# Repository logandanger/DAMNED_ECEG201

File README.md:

# DAMNED_ECEG201

Interactive OS and desktop simulator for DANGER, prototype #1: a generative beat maker built on preloaded samples. The hardware is the Bucknell ECEG 201 DAMNED board (ESP32-S3) plus Adafruit I2C breakouts.

This README is the single reference for the circuit. Everything below was extracted from the KiCad files in `hardware/kicad/` (the netlist is generated from the `.kicad_pcb`, so it reflects the routed board). Items marked **[verify]** were not provable from the files and need a check on the physical board or datasheet.

## Contents

1. [Repo layout](#1-repo-layout)
2. [Prototype #1 concept](#2-prototype-1-concept), [behavior](#beat-maker-behavior), [control map](#control-map)
3. [System block diagram](#3-system-block-diagram)
4. [Power](#4-power)
5. [ESP32-S3 module and pin map](#5-esp32-s3-module-and-pin-map)
6. [Display](#6-display)
7. [Buttons, slide switch, debounce](#7-buttons-slide-switch-and-debounce)
8. [I2C bus and add-on devices](#8-i2c-bus-and-add-on-devices)
9. [Audio path](#9-audio-path)
10. [LEDs](#10-leds)
11. [USB-C](#11-usb-c)
12. [CAN bus](#12-can-bus)
13. [Connectors, headers, jumpers, test points](#13-connectors-headers-jumpers-and-test-points)
14. [Free resources](#14-free-resources)
15. [Risks and open issues](#15-risks-and-open-issues)
16. [Planned software architecture](#16-planned-software-architecture)
17. [Bill of materials](#17-bill-of-materials)
18. [Course context](#18-course-context)

---

## 1. Repo layout

| Path | Contents |
|---|---|
| `hardware/kicad/` | KiCad 10 project: `NewBoard PCB v1.10 - DA2 no LDO` (`.kicad_pro/.kicad_sch/.kicad_pcb/.kicad_prl`) and the `LEDs` sub-sheet `sheet1.kicad_sch`. File names keep their spaces because the `.kicad_pro` references them by name. |
| `hardware/netlist/netlist.json` | Every net with its pins `[ref, pad, pin function]`, extracted from the PCB. Machine-readable. |
| `hardware/netlist/esp32_pinmap.csv` | ESP32-S3 module pin, pin function, net. |
| `docs/prototype1-sketch.jpg` | Hand sketch of the prototype #1 layout and parts list. |
| `docs/DA2-PCB-Layout-in-KiCad.pdf` | Course assignment 2 (KiCad layout). |
| `docs/DA8-DAMNED-Assembly.pdf` | Course assignment 8 (assembly and CircuitPython test). |
| `docs/DAMNED-sensors-2026-11.pdf` | Course-approved Adafruit parts list. |
| `docs/controls.md` | Control mapping, A/B chord logic, conflicts. |
| `docs/architecture.md` | Software structure, real-time rules, CPU and RAM budgets. |
| `docs/mirror-protocol.md` | Framebuffer protocol for `--mirror`. |
| `core/` | Beat engine, sampler, reverb, UI, app logic, mirror protocol. No hardware access. |
| `core/config/beat_config.hpp` | Every tunable: commit time, fades, loop, grid, layers, mutation, drums, hold times. |
| `core/samples/sample_data.cpp` | Generated sample data (flash). Do not edit; run `tools/pack_samples.py`. |
| `samples/` | Source WAVs and `manifest.csv`. |
| `tools/` | `build_sim.py`, `make_samples.py` (placeholder set), `pack_samples.py` (WAV to C++). |
| `core/config/control_map.hpp` | Every control-to-function mapping. |
| `hal/` | `hal.hpp` interface; `esp32/` and `sim/` implementations. |
| `firmware/` | ESP-IDF entry point, tasks, mirror sender, PlatformIO project. |
| `sim/` | SDL2 simulator. |
| `tests/` | Unit tests, whole-app tests, benchmark. |

Assembly guide (not mirrored): <https://bucknellmakers.dozuki.com/Guide/DAMNED+Project+Assembly/144?lang=en>

## 2. Prototype #1 concept

Source: `docs/prototype1-sketch.jpg`.

- **Base:** DAMNED PCB (6 tactile buttons, 320x240 display, ESP32-S3).
- **Keys:** Adafruit AW9523 GPIO expander (16 pins) for a 12-key chromatic octave, plain on/off (no velocity in prototype #1; deferred).
- **Encoders:** two Adafruit I2C STEMMA QT rotary encoders (bottom right, position may change).
- **Audio:** Adafruit TLV320DAC3100 I2S DAC with headphone and speaker output, driving a mono enclosed 3 W 4 ohm speaker. The separate PAM8302 amp was dropped (the DAC3100 has its own class-D speaker driver).
- **Light strip:** 2x16 DotStar LEDs behind a foggy acrylic panel, under the screen.
- **Power:** USB-C only for prototype #1.
- **Sketch layout:** screen center; d-pad left; A/B right of screen; speaker grille top right; encoders bottom right; 12 keys across the bottom (7 white, 5 black).
- **Sound engine:** generative beat maker on preloaded samples. No synthesis on the device.

### Beat maker behavior

You play; the box turns what you played into a loop, adds drums, and keeps it slowly changing.

- **Loop:** 4 bars of 4/4 on a 16th grid, 64 steps. At tempo $B$ in BPM one step lasts $t_\text{step} = \frac{60}{4B}\ \text{s}$, e.g. 125 ms at 120 BPM. The transport always runs; the screen shows its position.
- **Melodic keys** (the 8 non-pad keys) play the current instrument at once, pitched from its sample: $f = f_\text{root} \cdot 2^{(n - n_\text{root})/12}$. Each instrument plays in its sample's register.
- **Seeding:** everything played on the melodic keys is captured. The seed commits after **5 s** with no key held (`kSeedIdleCommit`). Holding a key postpones the commit.
- **Quantize:** on commit each note moves to the nearest 16th and its length to whole steps (1 to 16). Timing never has to be right. If nothing is playing, the loop restarts so the first note played lands on bar 1, beat 1.
- **Accumulate:** playing again on the same instrument adds to the same layer (same pitch on the same step merges). Selecting another instrument commits a pending seed at once and starts a new layer on the next seed.
- **Fade-in:** new or added notes ramp both the chance of playing and their velocity from 12 % to 100 % over **8 bars** (`kFadeInBars`).
- **Generative loop:** the first full pass is your exact quantized seed. After that, at each loop start, a layer mutates with an intensity that ramps over 6 loops to about 1.5 changes per loop: drop a note, add a note, octave shift, rhythm nudge of $\pm 1$ step, passing tone, or restore a changed note to the seed. Added and passing notes use only pitches and pitch classes you played; octave shifts stay within one octave of your range. The more a layer drifts, the more likely it moves back toward the seed.
- **Drums** (generated, on the 4 pad samples): silent until the first seed commits, then fade in over 8 bars. Kick on beat 1 and 3, snare on 2 and 4, hats on quarters, 8ths or 16ths, crash at each 4-bar phrase start, occasional open cymbal, ghost snares when busy, a snare fill in the last beat of some phrases. Density follows how many distinct steps your seeds use, plus a slow random walk. Extra kicks land on your strongest notes (velocity and length). Drums fade out when every layer is cleared.
- **Layers:** up to **4** (`kMaxLayers`), each with its own seed, mutation state and fade. A 5th fades the oldest out over 8 bars. Switching instrument never cuts anything: held notes ring until released, old loops keep playing.
- **Audio:** 32-voice sampler, 44.1 kHz stereo out, 22.05 kHz mono samples in flash. Every start ramps in over 2 ms; stolen or choked voices fade over 6 ms. Layer fades and clears are gain ramps, so nothing clicks. A cheap stereo reverb (4 combs, 4 allpasses) runs on both targets.
- **Samples:** placeholders rendered offline by `tools/make_samples.py`: drums `kick`, `snare`, `hat`, `crash`; instruments `keys`, `pluck`, `bass`, `bell`, `marimba`, `pad` (looped). To use real samples, replace WAVs in `samples/`, edit `samples/manifest.csv` (root note, loop points, release), run `python tools/pack_samples.py`, rebuild. Total budget 1.5 MB of flash; the placeholders use 515 kB.

### Control map

| Control | Function |
|---|---|
| Keys C# D# F# G# (top-left 4) | Drum pads: kick, snare, hat, crash. Play live over the loop; never captured. |
| Keys C D E F G A A# B | Current instrument, live; captured as the seed |
| A tap | Next instrument (cursor; the name turns red) |
| A hold 0.6 s | Select the instrument under the cursor |
| B tap | Previous instrument |
| A + B, release after 1 s | Clear current layer (fade 1.5 s). With only a pending seed on a new instrument, it drops that seed instead. |
| A + B, hold 3 s | Clear everything (fade 2.5 s), drums stop |
| Left encoder | Reverb, 2 % per detent |
| Right encoder | BPM, 60 to 180, 1 per detent; glides, loop stays in sync |
| D-pad, encoder pushes | Unassigned |

Taps fire on release, so pressing A and B together never steps or selects; see `docs/controls.md` for the full chord logic. The screen shows instrument, BPM, reverb, the loop position across 4 bars, each layer with its fade state (red mark = the layer A+B clears), the seed countdown, and A/B hold progress with a mark at 1 s.

## 3. System block diagram

```mermaid
flowchart LR
  USB[USB-C J4] -->|+5V| ESD[USBLC6 U1]
  USB -->|VBUS| D4[B540C D4] --> VCC[VCC rail]
  BAT[Battery J1] --> Q1[PMOS Q1] --> VCC
  VCC --> LDO[TLV75733 U3] -->|JP2| V33[+3V3]
  V33 --> ESP[ESP32-S3-WROOM-1 U2]
  ESD -->|D+/D-| ESP
  ESP -- SPI + DC/RST/BL --> LCD[ST7789 320x240 via FFC J6]
  ESP -- I2C GPIO3/4 --> I2C{{I2C bus}}
  I2C --> ADC[MCP3221A5 0x4D]
  I2C --> J2[J2/J5/J8 STEMMA QT]
  J2 -.-> AW[AW9523 keys]
  J2 -.-> ENC[2x rotary encoders]
  J2 -.-> DAC[TLV320DAC3100]
  ESP -- I2S GPIO5/6/7 --> J3[J3 I2S port] -.-> DAC
  ESP -- GPIO17/18 --> LED[20x SK9822 on board]
  BTN[6 buttons] --> DB[MC14490 debounce U4] --> ESP
  ESP -- TWAI GPIO15/16 --> CAN[TCAN3414 IC2] --> J15[J15 CAN]
```

Dotted lines are off-board Adafruit breakouts from the prototype #1 plan.

## 4. Power

### Topology

```mermaid
flowchart LR
  VBUS[+5V from USB-C] --> D4[D4 B540C-13-F Schottky] --> VCC
  VBUS --> Q1G[Q1 gate]
  BATT[+BATT J1 pin 2] --> Q1D[Q1 drain]
  Q1S[Q1 source] --> VCC
  VCC --> U3[U3 TLV75733PDBV 3.3 V LDO] --> JP2 --> V33[+3V3]
  V33 -->|JP1 solder jumper| VESP[V_ESP = ESP32 3V3 pin]
```

- **+5V** is raw USB VBUS. U1 (USBLC6-2SC6) clamps it, C3 (0.1 uF) decouples it, and R9 (100 k) pulls it to ground.
- **VCC** is the system rail, fed from either USB through D4 or the battery through Q1:
  - **USB present:** VCC is about VBUS minus the Schottky drop. Q1's gate sits at VBUS, so Q1 is off. Its body diode is reverse biased, so the battery is isolated.
  - **USB absent:** R9 pulls Q1's gate to ground. Q1 (DMP2045U, P-channel) turns on, and VCC equals the battery voltage minus a small $I R_{DS(on)}$ drop.
  - This is a standard P-MOSFET plus Schottky power-path OR.
- **No charger.** The board does not charge the battery. J1 is a JST-PH 2-pin (`S2B-PH-K-S`): pin 1 GND, pin 2 +BATT. There is no reverse-polarity protection.
- **+3V3** comes from U3 (TLV75733PDBV, 3.3 V LDO, SOT-23-5). IN and EN are both tied to VCC (always on), and C5 (10 uF) is the output cap. JP2 (2-pin header, shunt) sits between U3 OUT and the +3V3 net, so you can pull the shunt and insert a meter or an external supply.
- **V_ESP** is the ESP32 module's 3V3 pin. It reaches +3V3 only through JP1 (solder jumper, **default open**). JP1 must be bridged for the module to power up from this board. It also lets you measure ESP current.
- **VCC (5 V class) feeds:** U3 input, all 20 SK9822 LEDs, D3 power LED, header J7. **+3V3 feeds:** the ESP32 (via JP1), MCP3221, TCAN3414, MC14490, the display, pull-ups, I2C ports, J9.
- **Decoupling:** +3V3: C1 22 uF, C7/C9 10 uF, C2/C8/C10 0.1 uF. VCC: Cin1 10 uF, plus 0.1 uF at each LED (C13-C32).

### Power indicators

| LED | Fed from | Series R | Approx. current |
|---|---|---|---|
| D1 blue (`LTST-C250TBKT`) | V_ESP | R3 68 ohm | ~6 mA |
| D2 green (`LTST-C230GKT`) | +3V3 | R7 120 ohm | ~10 mA |
| D3 green | VCC | R8 300 ohm | ~10 mA |

$$I = \frac{V_s - V_f}{R}, \qquad \text{e.g. } \frac{3.3\ \text{V} - 2.9\ \text{V}}{68\ \Omega} \approx 6\ \text{mA}$$

(Forward voltages are typical for blue/green SMD LEDs; check the datasheets.)

### Budget (planning numbers)

- USB-C sink with 5.1 k pull-downs: the source offers at least 500 mA (USB 2.0), usually 1.5 A at 5 V. No USB-PD.
- 20 SK9822 LEDs at full white draw roughly 20 x 60 mA = 1.2 A worst case. Keep brightness low or the rail will sag. **[verify]** the datasheet current per LED.
- The DAC3100 speaker amp at 3 W into 4 ohm needs a sizeable 5 V current. Powering it from the 3V3 STEMMA port limits output power. **[verify]** against Adafruit's board docs before choosing the supply.

## 5. ESP32-S3 module and pin map

U2 is an **ESP32-S3-WROOM-1** (dual-core Xtensa LX7, 240 MHz, Wi-Fi + BLE, native USB). The flash/PSRAM variant is not specified in the files **[verify]**: see risk R1 in section 15.

Full table: `hardware/netlist/esp32_pinmap.csv`.

| GPIO | Module pin | Net | Function |
|---|---|---|---|
| EN | 3 | RESET | Reset button SW2; R6 5.1 k pull-up, C4 1 uF |
| 0 | 27 | BOOT | Boot-mode button SW1 |
| 1 | 39 | GPIO1 | Header J12 pin 5 |
| 2 | 38 | DISP_BL | Display backlight (J6 pin 8) |
| 3 | 15 | I2C_SDA | I2C data (strapping pin, see note) |
| 4 | 4 | I2C_SCL | I2C clock |
| 5 | 5 | I2S_LRCLK | I2S word select (J3 pin 4) |
| 6 | 6 | I2S_SDATA | I2S data out (J3 pin 3) |
| 7 | 7 | I2S_BLCK | I2S bit clock (J3 pin 2) |
| 8 | 12 | A5 | MCP3221 analog input net, TP18, header J12 pin 6 |
| 9 | 17 | D9 | Header J12 pin 2 |
| 10 | 18 | SW_Sli | Slide switch S1 |
| 11 | 19 | SW_Do | Debounced Down |
| 12 | 20 | SW_Uo | Debounced Up |
| 13 | 21 | SW_Ro | Debounced Right |
| 14 | 22 | SW_Lo | Debounced Left |
| 15 | 8 | TWAI_RX | CAN RXD (TCAN3414) |
| 16 | 9 | TWAI_TX | CAN TXD (TCAN3414) |
| 17 | 10 | DS_CLK | LED chain clock |
| 18 | 11 | DS_DATA | LED chain data |
| 19 | 13 | USB_D- | USB (through U1) |
| 20 | 14 | USB_D+ | USB (through U1) |
| 21 | 23 | SW_Ao | Debounced A |
| 35 | 28 | SPI_MOSI | Shared SPI bus |
| 36 | 29 | SPI_SCK | Shared SPI bus |
| 37 | 30 | SPI_MISO | Shared SPI bus |
| 38 | 31 | UART_RX | Header J10 pin 1 |
| 39 | 32 | UART_TX | Header J10 pin 2 |
| 40 | 33 | DISP_DC | Display data/command |
| 41 | 34 | DISP_RST | Display reset |
| 42 | 35 | SPI_CS1 | Display chip select |
| 43 (TXD0) | 37 | SPI_CS3 | SPI port J14 chip select |
| 44 (RXD0) | 36 | SPI_CS2 | SPI port J13 chip select |
| 45 | 26 | GPIO45 | Header J12 pin 4 (strapping pin) |
| 46 | 16 | GPIO46 | Header J12 pin 1 (strapping pin) |
| 47 | 24 | SW_Bo | Debounced B |
| 48 | 25 | GPIO48 | Header J12 pin 3 |

Notes:
- GPIO0, 3, 45, 46 are strapping pins. Keep their boot-time levels in mind when attaching peripherals (GPIO3 has the I2C pull-up, which is harmless at boot).
- GPIO43/44 are the default UART0 console pins, repurposed here as SPI chip selects. Console output over UART0 is not available; use USB CDC (native USB) for logs.
- GPIO39-42 are the JTAG pins; the board uses them as UART and display control. Debug through the USB-Serial-JTAG peripheral instead.

## 6. Display

- **Panel:** 320x240, ST7789 driver, SPI, colour, no touch (`320x240_SPI_ST7789_FFC`, reference DISP1).
- **Connector:** J6, `FFC3B07-08-T`, 8-pin FFC. FFC connectors wear out; open and close them sparingly (assembly guide).

| J6 pin | Signal | ESP32 |
|---|---|---|
| 1 | GND | |
| 2 | 3V3 | |
| 3 | SCK | GPIO36 |
| 4 | MOSI | GPIO35 |
| 5 | RST | GPIO41 |
| 6 | DC | GPIO40 |
| 7 | CS | GPIO42 (SPI_CS1) |
| 8 | Backlight | GPIO2 |

- The backlight is driven straight from a GPIO (no transistor on the schematic), so PWM dimming works through the LEDC peripheral but the display's backlight current must stay within the GPIO limit **[verify]**.
- Framebuffer size: $320 \times 240 \times 2\ \text{B} = 153{,}600\ \text{B}$ (RGB565). A full frame at SPI 40 MHz takes $153{,}600 \times 8 / 40\times10^{6} \approx 31\ \text{ms}$, so 30 fps needs partial updates or a faster clock (the ST7789 usually tolerates 40 to 80 MHz **[verify]**). LVGL partial buffers and dirty-rectangle updates handle this.

## 7. Buttons, slide switch and debounce

Six tactile inputs are hardware-debounced by **U4, MC14490** (hex contact-bounce eliminator, SOIC-16). The debounce time is set by **C12 (100 pF)** across OSCIN/OSCOUT **[verify]** the exact delay in the MC14490 datasheet for 3.3 V.

| Button | Switch | Raw net (to U4 input) | Debounced net (U4 output) | GPIO |
|---|---|---|---|---|
| Up | SW5 `TS02-66-50` | SW_U (AIN pin 1) | SW_Uo (pin 15) | 12 |
| Down | SW6 | SW_D (FIN pin 10) | SW_Do (pin 6) | 11 |
| Left | SW3 | SW_L (CIN pin 3) | SW_Lo (pin 13) | 14 |
| Right | SW4 | SW_R (EIN pin 5) | SW_Ro (pin 11) | 13 |
| A | SW7 `ML1A-11JW` | SW_A (BIN pin 14) | SW_Ao (pin 2) | 21 |
| B | SW8 `ML1A-11JW` | SW_B (DIN pin 12) | SW_Bo (pin 4) | 47 |

- Each raw line has a **10 k pull-up to +3V3** (R12-R17) and the switch shorts it to GND. The debouncer is non-inverting, so **buttons read HIGH when released and LOW when pressed**.
- **No software debounce is needed** (and none should be added for these six).
- The d-pad (SW3-SW6) are tactile switches, the A/B (SW7/SW8) are the springier right-side buttons per the assembly guide.
- **S1 (`CSS-1310TB`)** is an SPDT slide switch: +3V3 on one throw, GND on the other, common to **GPIO10 (SW_Sli)**. It is not debounced (a slide switch does not need it).
- **SW1 (BOOT, GPIO0)** and **SW2 (RESET, EN)** are `TL3365AF180QG` tactile switches.

## 8. I2C bus and add-on devices

- **Bus:** SDA = GPIO3, SCL = GPIO4. On-board pull-ups R4/R5 = 10 k to +3V3. Each Adafruit breakout adds its own pull-ups in parallel, so the bus gets stiffer as you add boards. With about 5 boards, 3.3 V and a pull-up near 2 k, the low-level current is under 2 mA, within the 3 mA I2C limit. **[verify]** by measuring the actual pull-up total if edges look slow.
- **Test points:** TP1 (SDA), TP2 (SCL).
- **Ports:** three 4-pin JST-SH (`SM04B-SRSS-TB`, STEMMA QT pinout: GND, 3V3, SDA, SCL): **J2, J5, J8**. They are wired in parallel, so you can daisy-chain breakouts out of any of them.

| Device | I2C address | Where |
|---|---|---|
| MCP3221A5 12-bit ADC (IC1) | 0x4D (the "A5" variant) | On board; input net `A5` |
| AW9523 GPIO expander (prototype keys) | 0x58 default (0x58-0x5B by jumper) | Adafruit 4886, off board |
| Rotary encoder #1 (seesaw) | 0x36 default | Adafruit 4991, off board **[verify]** |
| Rotary encoder #2 (seesaw) | 0x37 (set address jumper) | Same board type **[verify]** |
| TLV320DAC3100 (audio) | 0x18 | Adafruit 6309, off board **[verify]** |

No address conflicts. Run I2C at 400 kHz. Poll the AW9523 using its **INT pin** if possible (not available over STEMMA QT; it is a separate wire) or at about 1 kHz from a dedicated task. Keep the I2C task separate from the audio task.

## 9. Audio path

The board itself has **no audio hardware**. It exposes the I2S signals on **J3** (JST-SH 4-pin):

| J3 pin | Signal | ESP32 GPIO |
|---|---|---|
| 1 | GND | |
| 2 | I2S_BLCK (bit clock) | GPIO7 |
| 3 | I2S_SDATA (data out) | GPIO6 |
| 4 | I2S_LRCLK (word select) | GPIO5 |

- **No power pin on J3**: the DAC board gets power from the STEMMA I2C port (3V3) or its own supply.
- **No MCLK is routed.** The TLV320DAC3100 can derive its internal clocks from BCLK using its PLL, so this works, but the driver must program the PLL over I2C (register page setup) before audio plays.
- **Single data line** (one I2S DOUT): enough for stereo out. No audio input path exists on this board.
- **Prototype #1 audio chain:** ESP32-S3 I2S -> TLV320DAC3100 -> headphone jack (stereo) and speaker driver (mono, 3 W 4 ohm enclosed speaker). The PAM8302 amp (analog input) is removed from the plan.
- **Sample-rate math:** with 16-bit stereo at 44.1 kHz the I2S bit clock is $f_{BCLK} = 2 \times 16 \times 44{,}100 = 1.4112\ \text{MHz}$, and the data rate is $176.4\ \text{kB/s}$. DMA buffers of 256 frames give a buffer latency of $256 / 44{,}100 \approx 5.8\ \text{ms}$.

## 10. LEDs

- **20 x SK9822-EC20** (D5-D24; 2x2 mm RGB with a clock line, APA102-compatible), daisy-chained on `DS_DATA` (GPIO18) and `DS_CLK` (GPIO17).
- Chain order: D5 -> D6 -> ... -> D24. The `LEDs` sub-sheet routes it as three links (`LED_Dlink1-3`/`LED_Clink1-3`). D24's output pads are unconnected (end of chain).
- Powered from **VCC** (5 V on USB), each with a 0.1 uF cap (C13-C32).
- The data and clock are **3.3 V logic into 5 V devices**. SK9822 high-level input is nominally $0.7 \times V_{DD} = 3.5\ \text{V}$ at $V_{DD} = 5\ \text{V}$, above the 3.3 V drive. Many parts work in practice, but it is out of spec. **[verify]** on the bench; a level shifter (e.g. 74AHCT125) is the fix. See risk R3.
- Course software uses CircuitPython `adafruit_dotstar` on these pins.
- **Mismatch with the sketch:** the sketch shows a 2x16 DotStar panel (32 LEDs); the board has 20. The extra LEDs need an external strip chained from D24's unused SDO/CKO pads or a separate output. See risk R4.

## 11. USB-C

- **J4:** JAE `UJ20-C-H-G-SMT-1-P16-TR`, 16-pin USB-C receptacle (USB 2.0 only).
- **CC1/CC2:** 5.1 k to GND each (R1, R2). This presents the board as a **sink** (UFP) and requests default power.
- **Data:** the connector's D+/D- (both flip orientations, A6/B6 and A7/B7) join into `rawUSB_D+/D-`, go through **U1 (USBLC6-2SC6)** ESD protection, and reach the ESP32-S3's native USB (GPIO20 D+, GPIO19 D-).
- **Test points:** TP3/TP4 (raw D+/D-), TP5/TP6 (post-ESD D+/D-).
- **USB routing:** a `USB_differential` net class (0.142 mm width, 0.1 mm gap, 90 ohm target, `USB_diff_tuning` profile) is defined in the KiCad project.
- SBU pins and shield pads are unconnected.
- **Use:** flashing, USB CDC serial, and USB-MIDI device (the ESP32-S3 can enumerate as MIDI or composite). This is how prototype #1 will talk to a DAW.

## 12. CAN bus

- **IC2: TCAN3414** CAN FD transceiver, 3.3 V. TXD = GPIO16 (`TWAI_TX`), RXD = GPIO15 (`TWAI_RX`), STB tied to GND (always active), VCC = +3V3. `SHDNVIO` (pin 5) is unconnected.
- **J15** (`B2B-PH-K-S`, 2-pin): pin 1 CANH, pin 2 CANL.
- **Split termination:** JP3 and JP4 (solder jumpers) connect CANH and CANL to R10 and R11 (62 ohm each, about 124 ohm total), whose midpoint goes through C11 (4.7 nF) to GND. Close both jumpers at the end of a bus, leave them open elsewhere.
- Not part of prototype #1. Unused GPIO15/16 can be repurposed if the transceiver is not populated.

## 13. Connectors, headers, jumpers and test points

| Ref | Part | Use |
|---|---|---|
| J1 | JST-PH 2-pin (S2B-PH-K-S) | Battery: pin 1 GND, pin 2 +BATT |
| J2, J5, J8 | SH 4-pin STEMMA QT | I2C (GND, 3V3, SDA, SCL) |
| J3 | SH 4-pin | I2S: GND, BCLK, DATA, LRCLK |
| J4 | USB-C | Power and data |
| J6 | 8-pin FFC | Display |
| J7 | 1x2 socket | VCC (5 V class) out |
| J9 | 1x2 socket | +3V3 out |
| J10 | 1x2 socket | UART: pin 1 RX (GPIO38), pin 2 TX (GPIO39) |
| J11 | 1x4 socket | GND |
| J12 | 1x6 socket | 1 GPIO46, 2 GPIO9, 3 GPIO48, 4 GPIO45, 5 GPIO1, 6 A5 (GPIO8) |
| J13 | SH 4-pin | SPI port #2: MISO, SCK, MOSI, CS2 (GPIO44) |
| J14 | SH 4-pin | SPI port #3: MISO, SCK, MOSI, CS3 (GPIO43) |
| J15 | PH 2-pin | CAN: CANH, CANL |
| JP1 | Solder jumper | V_ESP to +3V3 (bridge to power the ESP32) |
| JP2 | 2-pin header + shunt | LDO output to +3V3 |
| JP3, JP4 | Solder jumpers | CAN split termination |
| H1-H4 | 2.5 mm holes | Mounting |

**Test points:** TP1 SDA, TP2 SCL, TP3/TP4 raw USB D+/D-, TP5/TP6 USB D+/D-, TP11 +3V3, TP12 LDO out, TP18 A5, TP21/TP22 SW_A/SW_Ao, TP24/TP25 SW_D/SW_Do, TP28 VCC; TP14-TP17, TP19, TP20, TP23, TP26 are GND.

**Board:** 2-layer, 1.6 mm FR-4, outline 120 mm x 55 mm. Default track 0.2 mm, power class 0.53 mm, vias 0.6/0.3 mm.

## 14. Free resources

- **GPIOs on header J12:** GPIO1, 9, 45, 46, 48 (watch strapping on 45/46) and GPIO8 (A5, ADC-capable).
- **SPI ports J13/J14** on the shared SPI bus (GPIO35/36/37) with separate chip selects: use J13 for a microSD card reader (sample storage; the course list includes Adafruit 4682).
- **Free I2C ports:** J2, J5, J8, chainable.
- **CAN pins** (GPIO15/16) and **UART** (GPIO38/39, header J10) if not used.
- **ADC:** MCP3221 (12-bit, I2C, 3.3 V reference) for one slow analog control; the ESP32-S3's own ADC is available on GPIO1 and GPIO8-10 (ADC1).
- **Native USB** for MIDI and mass storage.

## 15. Risks and open issues

| ID | Issue | Why it matters | Action |
|---|---|---|---|
| R1 | SPI uses **GPIO35, 36, 37** | On ESP32-S3-WROOM-1 variants with **octal PSRAM** (the "R8" modules), these pins are reserved for the PSRAM. The display bus would not work on those modules. The course board works, so the installed module probably has none or quad PSRAM. | **[verify]** the module's printed part number (e.g. N4, N8, N16 vs N8R8). It also decides how much RAM is free; the samples themselves live in flash. |
| R2 | USB-C 500 mA to 1.5 A budget | LEDs plus DAC speaker amp may exceed it. | Cap LED brightness; check the amp's current at 3 W. |
| R3 | LED logic level (3.3 V into 5 V SK9822) | Out of spec; flaky on some parts. | Test; add 74AHCT125 if needed. |
| R4 | 20 on-board LEDs vs the sketch's 2x16 (32) strip | Different count. | Decide: external 32-LED strip on D24's chain, or redesign. |
| R5 | No MCLK to the DAC | Needs PLL programming from BCLK. | Use a library/driver that configures the DAC3100 PLL from BCLK. |
| R6 | No battery charger, no reverse protection | Prototype #1 is USB-only, so no issue yet. | Add a charger IC (e.g. MCP73831) in a later PCB. |
| R7 | Keys are on/off only | No velocity. | Deferred. Later: two-contact keys and a second AW9523 (24 inputs), velocity from the time between contacts. |
| R8 | Encoder/DAC addresses and Adafruit product IDs | Marked **[verify]** above. | Check on arrival with an I2C scan. |
| R9 | The filename says "no LDO" but U3 (TLV75733) is on the netlist | Unclear which course variant this is. | Confirm what is actually populated on your board. |
| R10 | AW9523 has no internal pull-ups | The 12 keys read as floating inputs without them. | Fit an external pull-up, about 10 k to 3V3, on each key line. Firmware assumes active-low. |

## 16. Planned software architecture

- **Language and tooling:** C++, PlatformIO with ESP-IDF underneath, LVGL for the UI at 320x240.
- **Simulator:** the same app code compiled for desktop with SDL2 (an on-screen replica with the same number of controls: 12 keys, 6 buttons, 2 encoders, a DotStar strip preview). Roughly laid out like the sketch; function mapping is up to the designer.
- **Shape:**
  - `hal/`: hardware abstraction (display, keys, encoders, buttons, LEDs, audio out). One implementation for ESP32, one for the simulator.
  - `core/`: UI, app logic, beat engine (sampler, seeds, layers, drums, reverb).
  - `firmware/`: ESP-IDF entry point and drivers.
  - `sim/`: SDL2 desktop build.
- **Real-time rules:** audio on its own task, pinned to a core, fed by I2S DMA. I2C polling in a separate task. UI on the other core. No allocation in the audio callback.
- **Input layer:** key events carry a velocity field (fixed value for now) so velocity-sensitive keys can be added without a rewrite.
- **Buttons:** read the six debounced GPIOs as active-low; no software debounce.
- **Course firmware:** the DAMNED course software is CircuitPython (libraries: `adafruit_st7789`, `adafruit_dotstar`, `cp_mcp3x21`, `button_handler`, `adafruit_display_text`). It is useful for quick bring-up tests of the same pins. The production OS here is C++.

Status: beat engine, UI and simulator run on the PC. Firmware compiles for the ESP32-S3 but has not run on hardware, and the DAC driver is not written. See `docs/architecture.md`.

### Run the simulator

Needs only Python. The script fetches a private, pinned compiler, CMake and Ninja, builds, and runs the tests. Its files go to `~/.danger-build`, outside OneDrive.

```
python tools/build_sim.py
build/danger_sim
```

| Flag | Mode |
|---|---|
| (none) | Full replica with audio |
| `--screen-only` | Only the 320x240 UI; add `--scale 2` to enlarge |
| `--mirror COM5` | Live screen of the real device over USB |
| `--help` | Lists all flags |

Computer keyboard: `A S D F G H J` and `U` melodic, `W E T Y` pads, `X` = A, `Z` = B, `K`/`L` reverb, `,`/`.` BPM. Mouse: click keys and buttons; right-click a button to latch it (A+B with one pointer); drag or scroll an encoder. Full list: `docs/controls.md`. Esc quits.

### Build the firmware

```
cd firmware
pio run -e danger              # with screen mirror
pio run -e danger-nomirror     # without
```

Needs `pip install platformio`. Pinned to `espressif32@8.0.0`, which brings ESP-IDF 6.1. Set `PLATFORMIO_WORKSPACE_DIR` to a folder outside OneDrive, or the build tree gets synced.

## 17. Bill of materials

On-board (from the schematic):

| Ref | Value / part | Qty |
|---|---|---|
| U2 | ESP32-S3-WROOM-1 | 1 |
| U3 | TLV75733PDBV, 3.3 V LDO | 1 |
| U4 | MC14490DWR2G, hex debouncer | 1 |
| U1 | USBLC6-2SC6, USB ESD | 1 |
| IC1 | MCP3221A5T-I/OT, 12-bit I2C ADC | 1 |
| IC2 | TCAN3414DDFR, CAN FD transceiver | 1 |
| Q1 | DMP2045U-7, P-MOSFET | 1 |
| D4 | B540C-13-F, 5 A Schottky | 1 |
| D1 | LTST-C250TBKT, blue LED | 1 |
| D2, D3 | LTST-C230GKT, green LED | 2 |
| D5-D24 | SK9822-EC20, RGB LED | 20 |
| DISP1 | 320x240 ST7789 SPI, FFC | 1 |
| SW1, SW2 | TL3365AF180QG | 2 |
| SW3-SW6 | TS02-66-50-BK-100-SCR-D | 4 |
| SW7, SW8 | ML1A-11JW | 2 |
| S1 | CSS-1310TB slide switch | 1 |
| R1, R2, R6 | 5.1 k | 3 |
| R3 / R7 / R8 | 68 / 120 / 300 ohm | 1 each |
| R4, R5, R12-R17 | 10 k | 8 |
| R9 | 100 k | 1 |
| R10, R11 | 62 ohm | 2 |
| C1 | 22 uF | 1 |
| C5, C7, C9, Cin1 | 10 uF | 4 |
| C4 | 1 uF | 1 |
| C11 | 4.7 nF | 1 |
| C12 | 100 pF | 1 |
| C2, C3, C8, C10, C13-C32 | 0.1 uF | 24 |
| J1-J15, JP1-JP4, TP1-TP28 | connectors, jumpers, test points | see section 13 |

Prototype #1 add-ons (Adafruit, from the sketch and course sensor sheet):

| Part | Adafruit ID | Note |
|---|---|---|
| AW9523 GPIO expander | 4886 | $4.95 each. 16 pins; 4 addresses 0x58-0x5B. Keys. |
| I2C rotary encoder (x2) | 4991 | seesaw, STEMMA QT **[verify]** variant |
| TLV320DAC3100 I2S DAC | 6309 | Headphone + speaker driver |
| Mono enclosed 3 W 4 ohm speaker | | Speaker |
| ~~PAM8302 amp~~ | ~~2130~~ | Removed (redundant) |

## 18. Course context

- ECEG 201 (Fall 2026), Bucknell University. This board is the course's DAMNED project, an ESP32-S3 IoT device. DA2 covers PCB layout in KiCad; DA8 covers assembly and CircuitPython testing.
- The DA8 integration test exercises: LCD text and graphics, the MCP3221 ADC (input jumpered to GND reads 0 V), the DotStar LEDs, Wi-Fi, and the six buttons.
- The course sensor sheet (`docs/DAMNED-sensors-2026-11.pdf`) lists approved Adafruit parts. Relevant ones: AW9523 (4886), rotary encoder (4991), TLV320DAC3100 (6309), MAX98357A (3006), UDA1334 (3678), MIDI FeatherWing (4740), MPR121 capacitive touch (1982), TCA8418 keypad scanner, uSD reader (4682). None of the listed sensors measures key velocity.

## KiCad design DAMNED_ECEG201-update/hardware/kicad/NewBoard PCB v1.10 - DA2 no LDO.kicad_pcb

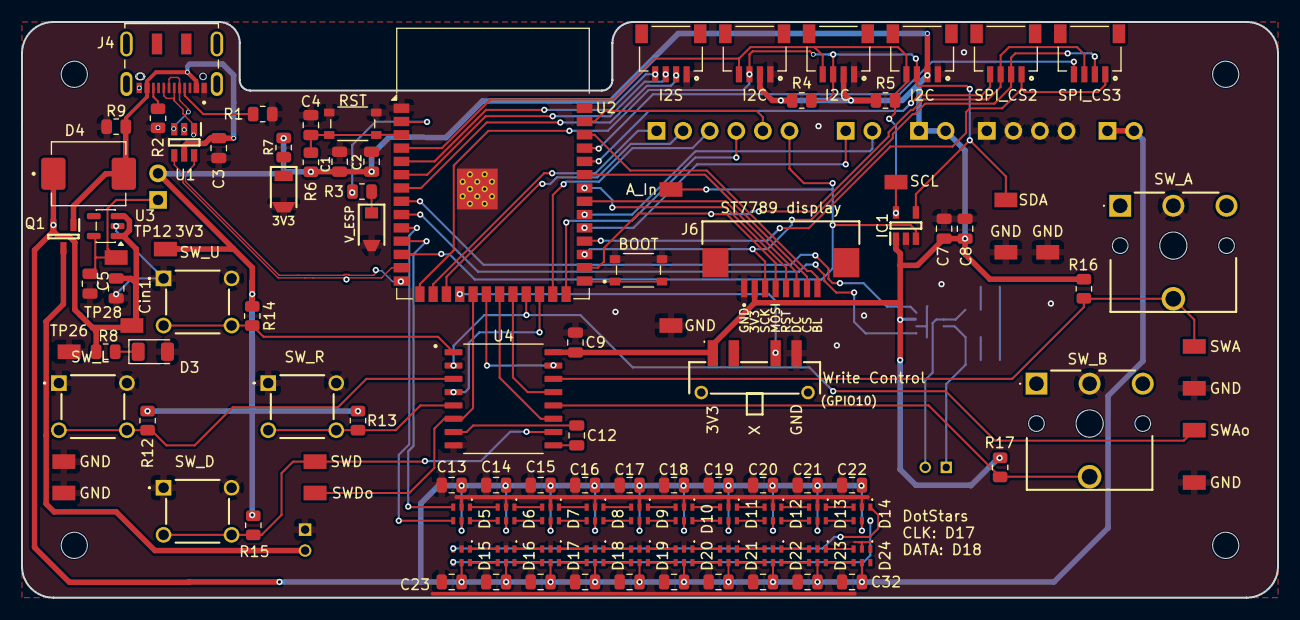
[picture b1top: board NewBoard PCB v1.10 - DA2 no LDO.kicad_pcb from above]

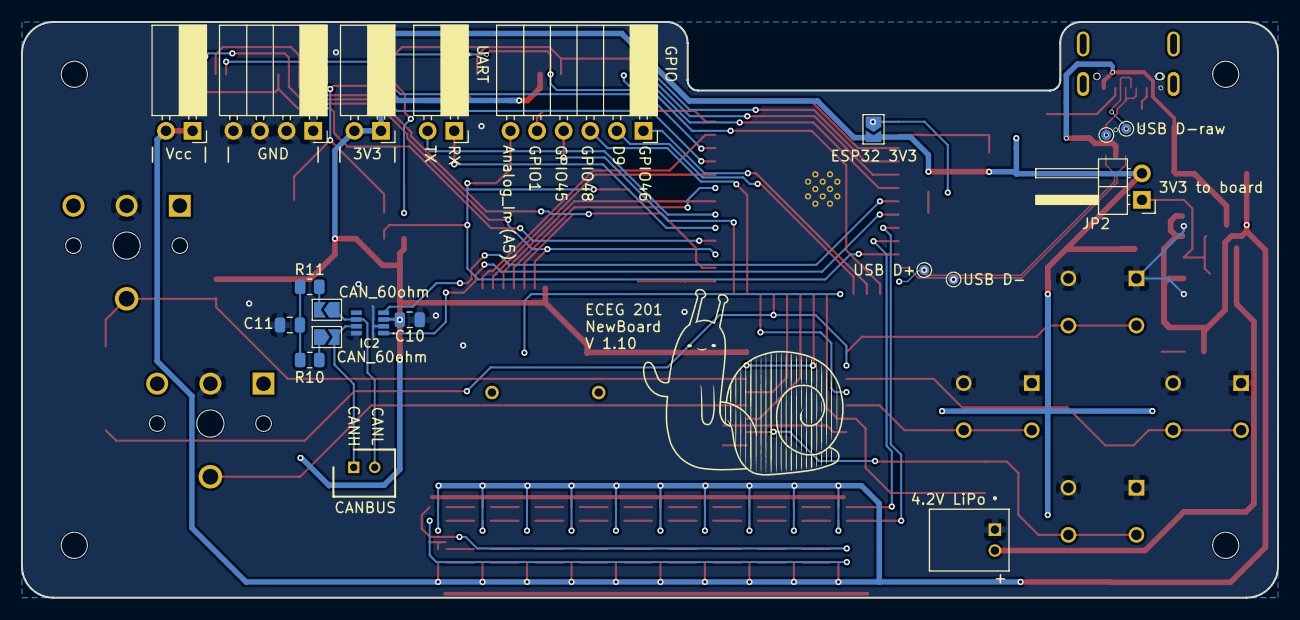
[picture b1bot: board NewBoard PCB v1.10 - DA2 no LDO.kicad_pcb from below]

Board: 2 copper layers, 120.0 x 55.0 mm, 135 parts (20 on the bottom side), 102 nets.

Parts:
C1: 22u; C_0805_2012Metric
C2, C3, C8, C10, C13, C14, C15, C16, C17, C18, C19, C20, C21, C22, C23, C24, C25, C26, C27, C28, C29, C30, C31, C32: 0.1u; C_0805_2012Metric
C4: 1u; C_0805_2012Metric
C5, C7, C9: 10u; C_0805_2012Metric
C11: 4.7n; C_0805_2012Metric
C12: 100p; C_0805_2012Metric
Cin1: 10u; C_0805_2012Metric
D1: LTST-C250TBKT
D2: LTST-C230GKT
D3: LTST-C230GKT; LED_1206_3216Metric
D4: B540C-13-F
D5, D6, D7, D8, D9, D10, D11, D12, D13, D14, D15, D16, D17, D18, D19, D20, D21, D22, D23, D24: SK9822-EC20
DISP1: 320x240_SPI_ST7789_FFC
H1, H2, H3, H4: MountingHole; MountingHole_2.5mm
IC1: MCP3221A5T-I_OT; SOT95P280X145-5N
IC2: TCAN3414DDFR
J1: S2B-PH-K-S
J2, J5, J8: SM04B-SRSS-TB (STEMMA_QT); SM04B-SRSS-TB
J3, J13, J14: SM04B-SRSS-TB
J4: UJ20-C-H-G-SMT-1-P16-TR; JAE_DX07S016JA1R1500
J6: FFC3B07-08-T
J7, J9, J10: SSW­102­02­T­S­RA; PinSocket_1x02_P2.54mm_Horizontal
J11: SSW­104­02­T­S­RA; PinSocket_1x04_P2.54mm_Horizontal
J12: SSW­106­02­T­S­RA; PinSocket_1x06_P2.54mm_Horizontal
J15: B2B-PH-K-S
JP1: SolderJumper_2_Open; SolderJumper-2_P1.3mm_Open_TrianglePad1.0x1.5mm
JP2: HMTSW-102-08-S-S-220-RA; PinHeader_1x02_P2.54mm_Horizontal
JP3, JP4: Jumper_2_Open; SolderJumper-2_P1.3mm_Open_TrianglePad1.0x1.5mm
Q1: DMP2045U-7; SOT96P240X115-3N
R1, R2, R6: 5.1k; R_0805_2012Metric
R3: 68; R_0805_2012Metric
R4, R5, R12, R13, R14, R15, R16, R17: 10k; R_0805_2012Metric
R7: 120; R_0805_2012Metric
R8: 300; R_0805_2012Metric
R9: 100k; R_0805_2012Metric
R10, R11: 62; R_0805_2012Metric
S1: CSS-1310TB
SW1, SW2: TL3365AF180QG; SW_TL3365AF180QG
SW3, SW4, SW5, SW6: TS02-66-50-BK-100-SCR-D
SW7, SW8: ML1A-11JW
TP1, TP2, TP11, TP12, TP14, TP15, TP16, TP17, TP18, TP19, TP20, TP21, TP22, TP23, TP24, TP25, TP26, TP28: S2751-46R
TP3, TP4, TP5, TP6: TestPoint; TestPoint_Pad_D1.0mm
U1: USBLC6-2SC6; SOT95P280X145-6N
U2: ESP32-S3-WROOM-1
U3: TLV75733PDBV; SOT-23-5
U4: MC14490DWR2G; SOIC127P1030X265-16N

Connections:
+3V3: C1.1, C2.1, C7.1, C8.1, C9.1, C10.1, IC1.1 (VDD), IC2.3 (VCC), J2.2 (3V3), J5.2 (3V3), J6.2, J8.2 (3V3), J9.1, J9.2, JP1.2 (B), JP2.2 (B), R4.1, R5.1, R6.1, R7.1, R12.1, R13.1, R14.1, R15.1, R16.1, R17.1, S1.1, TP11.1 (1_1), U4.16 (VDD)
+5V: C3.1, D4.A, J4.A4/B9 (VBUS), J4.B4/A9 (VBUS), Q1.1 (G), R9.1, U1.5 (Vbus)
+BATT: J1.2, Q1.3 (D)
/LEDs/LED_Clink1: D9.6 (CKO), D10.4 (CKI)
/LEDs/LED_Clink2: D14.6 (CKO), D15.4 (CKI)
/LEDs/LED_Clink3: D19.6 (CKO), D20.4 (CKI)
/LEDs/LED_Dlink1: D9.1 (SDO), D10.3 (SDI)
/LEDs/LED_Dlink2: D14.1 (SDO), D15.3 (SDI)
/LEDs/LED_Dlink3: D19.1 (SDO), D20.3 (SDI)
/NewBoard PCB v1.10 - DA2 no LDO/A5: IC1.3 (AIN), J12.6, TP18.1 (1_1), U2.12 (IO8)
/NewBoard PCB v1.10 - DA2 no LDO/BOOT: SW1.1, SW1.2, U2.27 (IO0)
/NewBoard PCB v1.10 - DA2 no LDO/CANH: IC2.7 (CANH), J15.1, JP3.2 (B)
/NewBoard PCB v1.10 - DA2 no LDO/CANL: IC2.6 (CANL), J15.2, JP4.1 (A)
/NewBoard PCB v1.10 - DA2 no LDO/CC1: J4.A5 (CC1), R1.1
/NewBoard PCB v1.10 - DA2 no LDO/CC2: J4.B5 (CC2), R2.1
/NewBoard PCB v1.10 - DA2 no LDO/D9: J12.2, U2.17 (IO9)
/NewBoard PCB v1.10 - DA2 no LDO/DISP_BL: J6.8, U2.38 (IO2)
/NewBoard PCB v1.10 - DA2 no LDO/DISP_DC: J6.6, U2.33 (IO40)
/NewBoard PCB v1.10 - DA2 no LDO/DISP_RST: J6.5, U2.34 (IO41)
/NewBoard PCB v1.10 - DA2 no LDO/GPIO1: J12.5, U2.39 (IO1)
/NewBoard PCB v1.10 - DA2 no LDO/GPIO45: J12.4, U2.26 (IO45)
/NewBoard PCB v1.10 - DA2 no LDO/GPIO46: J12.1, U2.16 (IO46)
/NewBoard PCB v1.10 - DA2 no LDO/GPIO48: J12.3, U2.25 (IO48)
/NewBoard PCB v1.10 - DA2 no LDO/I2C_SCL: IC1.5 (SCL), J2.4 (SCL), J5.4 (SCL), J8.4 (SCL), R5.2, TP2.1 (1_1), U2.4 (IO4)
/NewBoard PCB v1.10 - DA2 no LDO/I2C_SDA: IC1.4 (SDA), J2.3 (SDA), J5.3 (SDA), J8.3 (SDA), R4.2, TP1.1 (1_1), U2.15 (IO3)
/NewBoard PCB v1.10 - DA2 no LDO/I2S_BLCK: J3.2, U2.7 (IO7)
/NewBoard PCB v1.10 - DA2 no LDO/I2S_LRCLK: J3.4, U2.5 (IO5)
/NewBoard PCB v1.10 - DA2 no LDO/I2S_SDATA: J3.3, U2.6 (IO6)
/NewBoard PCB v1.10 - DA2 no LDO/RESET: C4.1, R6.2, SW2.1, SW2.2, U2.3 (EN)
/NewBoard PCB v1.10 - DA2 no LDO/SPI_CS1: J6.7, U2.35 (IO42)
/NewBoard PCB v1.10 - DA2 no LDO/SPI_CS2: J13.4, U2.36 (RXD0)
/NewBoard PCB v1.10 - DA2 no LDO/SPI_CS3: J14.4, U2.37 (TXD0)
/NewBoard PCB v1.10 - DA2 no LDO/SPI_MISO: J13.1, J14.1, U2.30 (IO37)
/NewBoard PCB v1.10 - DA2 no LDO/SPI_MOSI: J6.4, J13.3, J14.3, U2.28 (IO35)
/NewBoard PCB v1.10 - DA2 no LDO/SPI_SCK: J6.3, J13.2, J14.2, U2.29 (IO36)
/NewBoard PCB v1.10 - DA2 no LDO/SW_A: R16.2, SW7.4, TP21.1 (1_1), U4.14 (BIN)
/NewBoard PCB v1.10 - DA2 no LDO/SW_Ao: TP22.1 (1_1), U2.23 (IO21), U4.2 (BOUT)
/NewBoard PCB v1.10 - DA2 no LDO/SW_B: R17.2, SW8.4, U4.12 (DIN)
/NewBoard PCB v1.10 - DA2 no LDO/SW_Bo: U2.24 (IO47), U4.4 (DOUT)
/NewBoard PCB v1.10 - DA2 no LDO/SW_D: R15.2, SW6.3, SW6.4, TP24.1 (1_1), U4.10 (FIN)
/NewBoard PCB v1.10 - DA2 no LDO/SW_Do: TP25.1 (1_1), U2.19 (IO11), U4.6 (FOUT)
/NewBoard PCB v1.10 - DA2 no LDO/SW_L: R12.2, SW3.3, SW3.4, U4.3 (CIN)
/NewBoard PCB v1.10 - DA2 no LDO/SW_Lo: U2.22 (IO14), U4.13 (COUT)
/NewBoard PCB v1.10 - DA2 no LDO/SW_R: R13.2, SW4.3, SW4.4, U4.5 (EIN)
/NewBoard PCB v1.10 - DA2 no LDO/SW_Ro: U2.21 (IO13), U4.11 (EOUT)
/NewBoard PCB v1.10 - DA2 no LDO/SW_Sli: S1.3, U2.18 (IO10)
/NewBoard PCB v1.10 - DA2 no LDO/SW_U: R14.2, SW5.3, SW5.4, U4.1 (AIN)
/NewBoard PCB v1.10 - DA2 no LDO/SW_Uo: U2.20 (IO12), U4.15 (AOUT)
/NewBoard PCB v1.10 - DA2 no LDO/TWAI_RX: IC2.4 (RXD), U2.8 (IO15)
/NewBoard PCB v1.10 - DA2 no LDO/TWAI_TX: IC2.1 (TXD), U2.9 (IO16)
/NewBoard PCB v1.10 - DA2 no LDO/UART_RX: J10.1, U2.31 (IO38)
/NewBoard PCB v1.10 - DA2 no LDO/UART_TX: J10.2, U2.32 (IO39)
/NewBoard PCB v1.10 - DA2 no LDO/USB_D+: TP5.1 (1_1), U1.6 (D+out), U2.14 (USB_D+)
/NewBoard PCB v1.10 - DA2 no LDO/USB_D-: TP6.1 (1_1), U1.4 (D-out), U2.13 (USB_D-)
/NewBoard PCB v1.10 - DA2 no LDO/V_ESP: JP1.1 (A), R3.1, U2.2 (3V3)
/NewBoard PCB v1.10 - DA2 no LDO/rawUSB_D+: J4.A6 (D+), J4.B6 (D+), TP3.1 (1_1), U1.1 (D+in)
/NewBoard PCB v1.10 - DA2 no LDO/rawUSB_D-: J4.A7 (D-), J4.B7 (D-), TP4.1 (1_1), U1.3 (D-in)
DS_CLK: D5.4 (CKI), U2.10 (IO17)
DS_DATA: D5.3 (SDI), U2.11 (IO18)
GND: C1.2, C2.2, C3.2, C4.2, C5.2, C7.2, C8.2, C9.2, C10.2, C11.1, C13.2, C14.2, C15.2, C16.2, C17.2, C18.2, C19.2, C20.2, C21.2, C22.2, C23.2, C24.2, C25.2, C26.2, C27.2, C28.2, C29.2, C30.2, C31.2, C32.2, Cin1.2, D1.2 (K), D2.2 (K), D3.2 (K), D5.2 (GND), D6.2 (GND), D7.2 (GND), D8.2 (GND), D9.2 (GND), D10.2 (GND), D11.2 (GND), D12.2 (GND), D13.2 (GND), D14.2 (GND), D15.2 (GND), D16.2 (GND), D17.2 (GND), D18.2 (GND), D19.2 (GND), D20.2 (GND), D21.2 (GND), D22.2 (GND), D23.2 (GND), D24.2 (GND), IC1.2 (VSS), IC2.2 (GND), IC2.8 (STB), J1.1, J2.1 (GND), J3.1, J4.A1/B12 (GND), J4.B1/A12 (GND), J5.1 (GND), J6.1, J8.1 (GND), J11.1, J11.2, J11.3, J11.4, R1.2, R2.2, R9.2, S1.4, SW1.3, SW1.4, SW2.3, SW2.4, SW3.1, SW3.2, SW4.1, SW4.2, SW5.1, SW5.2, SW6.1, SW6.2, SW7.2, SW8.2, TP14.1 (1_1), TP15.1 (1_1), TP16.1 (1_1), TP17.1 (1_1), TP19.1 (1_1), TP20.1 (1_1), TP23.1 (1_1), TP26.1 (1_1), U1.2 (GND), U2.1 (GND), U2.40 (GND), U2.41 (GND), U3.2 (GND), U4.8 (VSS)
unnamed: C11.2, R10.2, R11.1
unnamed: D1.1 (A), R3.2
unnamed: D2.1 (A), R7.2
unnamed: D3.1 (A), R8.2
unnamed: D5.6 (CKO), D6.4 (CKI)
unnamed: D5.1 (SDO), D6.3 (SDI)
unnamed: D6.6 (CKO), D7.4 (CKI)
unnamed: D6.1 (SDO), D7.3 (SDI)
unnamed: D7.6 (CKO), D8.4 (CKI)
unnamed: D7.1 (SDO), D8.3 (SDI)
unnamed: D8.6 (CKO), D9.4 (CKI)
unnamed: D8.1 (SDO), D9.3 (SDI)
unnamed: D10.6 (CKO), D11.4 (CKI)
unnamed: D10.1 (SDO), D11.3 (SDI)
unnamed: D11.6 (CKO), D12.4 (CKI)
unnamed: D11.1 (SDO), D12.3 (SDI)
unnamed: D12.6 (CKO), D13.4 (CKI)
unnamed: D12.1 (SDO), D13.3 (SDI)
unnamed: D13.6 (CKO), D14.4 (CKI)
unnamed: D13.1 (SDO), D14.3 (SDI)
unnamed: D15.6 (CKO), D16.4 (CKI)
unnamed: D15.1 (SDO), D16.3 (SDI)
unnamed: D16.6 (CKO), D17.4 (CKI)
unnamed: D16.1 (SDO), D17.3 (SDI)
unnamed: D17.6 (CKO), D18.4 (CKI)
unnamed: D17.1 (SDO), D18.3 (SDI)
unnamed: D18.6 (CKO), D19.4 (CKI)
unnamed: D18.1 (SDO), D19.3 (SDI)
unnamed: D20.6 (CKO), D21.4 (CKI)
unnamed: D20.1 (SDO), D21.3 (SDI)
unnamed: D21.6 (CKO), D22.4 (CKI)
unnamed: D21.1 (SDO), D22.3 (SDI)
unnamed: D22.6 (CKO), D23.4 (CKI)
unnamed: D22.1 (SDO), D23.3 (SDI)
unnamed: D23.6 (CKO), D24.4 (CKI)
unnamed: D23.1 (SDO), D24.3 (SDI)
unnamed: C5.1, JP2.1 (A), TP12.1 (1_1), U3.5 (OUT)
unnamed: JP3.1 (A), R10.1
unnamed: JP4.2 (B), R11.2
unnamed: C12.1, U4.7 (OSCIN)
unnamed: C12.2, U4.9 (OSCOUT)
VCC: C13.1, C14.1, C15.1, C16.1, C17.1, C18.1, C19.1, C20.1, C21.1, C22.1, C23.1, C24.1, C25.1, C26.1, C27.1, C28.1, C29.1, C30.1, C31.1, C32.1, Cin1.1, D4.C, D5.5 (VDD), D6.5 (VDD), D7.5 (VDD), D8.5 (VDD), D9.5 (VDD), D10.5 (VDD), D11.5 (VDD), D12.5 (VDD), D13.5 (VDD), D14.5 (VDD), D15.5 (VDD), D16.5 (VDD), D17.5 (VDD), D18.5 (VDD), D19.5 (VDD), D20.5 (VDD), D21.5 (VDD), D22.5 (VDD), D23.5 (VDD), D24.5 (VDD), J7.1, J7.2, Q1.2 (S), R8.1, TP28.1 (1_1), U3.1 (IN), U3.3 (EN)
